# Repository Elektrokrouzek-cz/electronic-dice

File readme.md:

# Electronic dice
This is the construction of electronic dice for RedNetCon technological conference
workshop. It is based on NE555 timer and 4017 logical circuit. All components are 
in THT packages.

PCB is 2-layer and was designed using KiCad 8. Fabrication output for JLCPCB is in gerber folder.

Happy soldering!

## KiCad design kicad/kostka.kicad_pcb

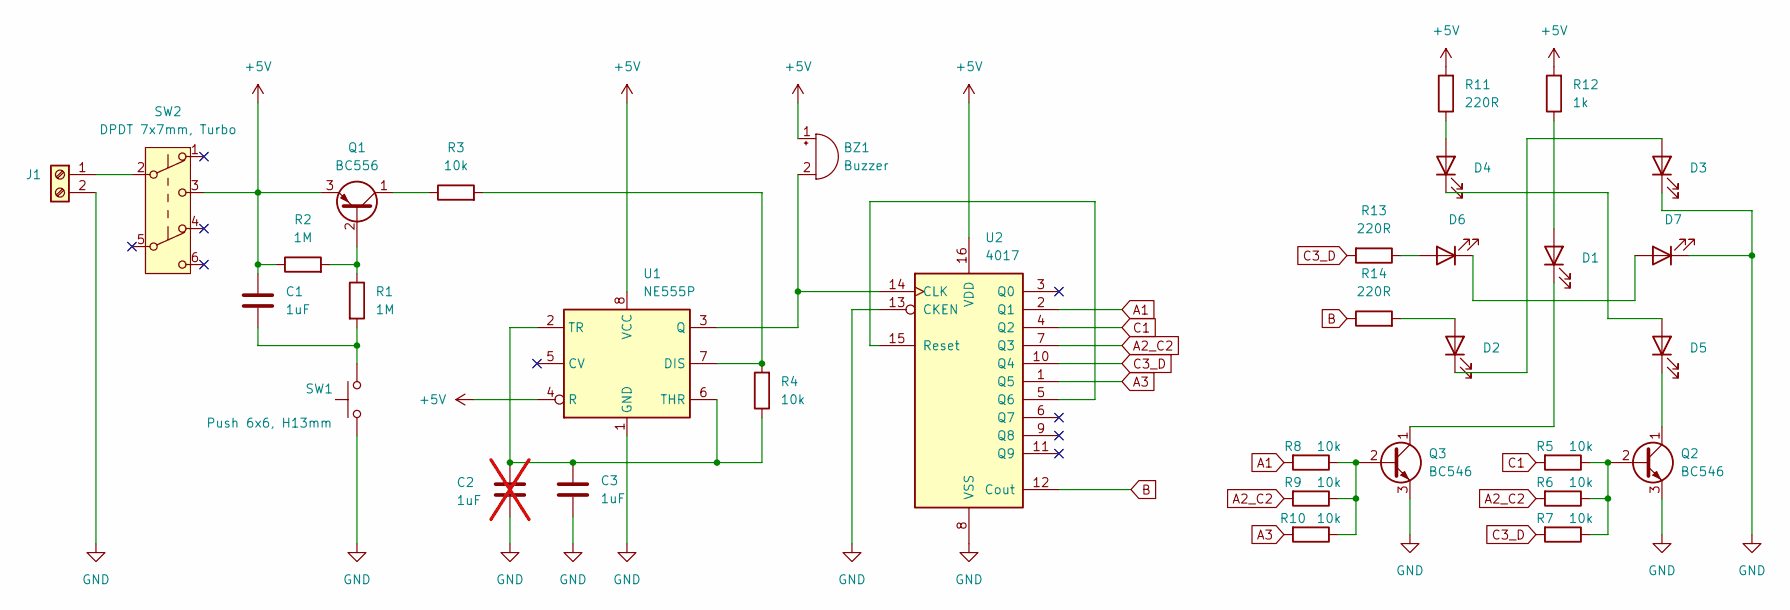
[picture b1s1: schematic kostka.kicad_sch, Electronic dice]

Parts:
BZ1: Buzzer; Buzzer_12x9.5RM7.6
C1, C3: 1uF; C_Disc_D4.3mm_W1.9mm_P5.00mm
C2: 1uF; C_Disc_D4.3mm_W1.9mm_P5.00mm; not fitted
D1, D2, D3, D4, D5, D6, D7: 5mm, R; LED_D5.0mm
J1: Screw_Terminal_01x02; TerminalBlock_4Ucon_1x02_P3.50mm_Horizontal
Q1: BC556; TO-92_Inline
Q2, Q3: BC546; TO-92_Inline
R1, R2: 1M; R_Axial_DIN0207_L6.3mm_D2.5mm_P7.62mm_Horizontal
R3, R4, R5, R6, R7, R8, R9, R10: 10k; R_Axial_DIN0207_L6.3mm_D2.5mm_P7.62mm_Horizontal
R11, R13, R14: 220R; R_Axial_DIN0207_L6.3mm_D2.5mm_P7.62mm_Horizontal
R12: 1k; R_Axial_DIN0207_L6.3mm_D2.5mm_P7.62mm_Horizontal
SW1: Push 6x6, H13mm; SW_PUSH_6mm_H13mm
SW2: DPDT 7x7mm, Turbo; SW_DPDT_7x7_Turbo
U1: NE555P; DIP-8_W7.62mm
U2: 4017; DIP-16_W7.62mm

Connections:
+5V: BZ1.1 (+), C1.1, Q1.3 (E), R2.1, R11.2, R12.2, SW2.3 (C), U1.4 (R), U1.8 (VCC), U2.16 (VDD)
A1: R8.2, U2.2 (Q1)
A2_C2: R6.2, R9.2, U2.7 (Q3)
A3: R10.2, U2.1 (Q5)
B: R14.1, U2.12 (Cout)
C1: R5.2, U2.4 (Q2)
C3_D: R7.2, R13.2, U2.10 (Q4)
GND: C2.2, C3.2, D3.1 (K), D7.1 (K), J1.2, Q2.3 (E), Q3.3 (E), SW1.1, U1.1 (GND), U2.8 (VSS), U2.13 (CKEN)
unnamed: BZ1.2 (-), U1.3 (Q), U2.14 (CLK)
unnamed: C1.2, R1.2, SW1.2
unnamed: D1.2 (A), R12.1
unnamed: D1.1 (K), Q3.1 (C)
unnamed: D2.2 (A), R14.2
unnamed: D2.1 (K), D3.2 (A)
unnamed: D4.2 (A), R11.1
unnamed: D4.1 (K), D5.2 (A)
unnamed: D5.1 (K), Q2.1 (C)
unnamed: D6.2 (A), R13.1
unnamed: D6.1 (K), D7.2 (A)
unnamed: J1.1, SW2.2 (B)
unnamed: Q1.2 (B), R1.1, R2.2
unnamed: Q1.1 (C), R3.1
unnamed: Q2.2 (B), R5.1, R6.1, R7.1
unnamed: Q3.2 (B), R8.1, R9.1, R10.1
unnamed: R3.2, R4.2, U1.7 (DIS)
unnamed: C2.1, C3.1, R4.1, U1.2 (TR), U1.6 (THR)
unnamed: U2.5 (Q6), U2.15 (Reset)

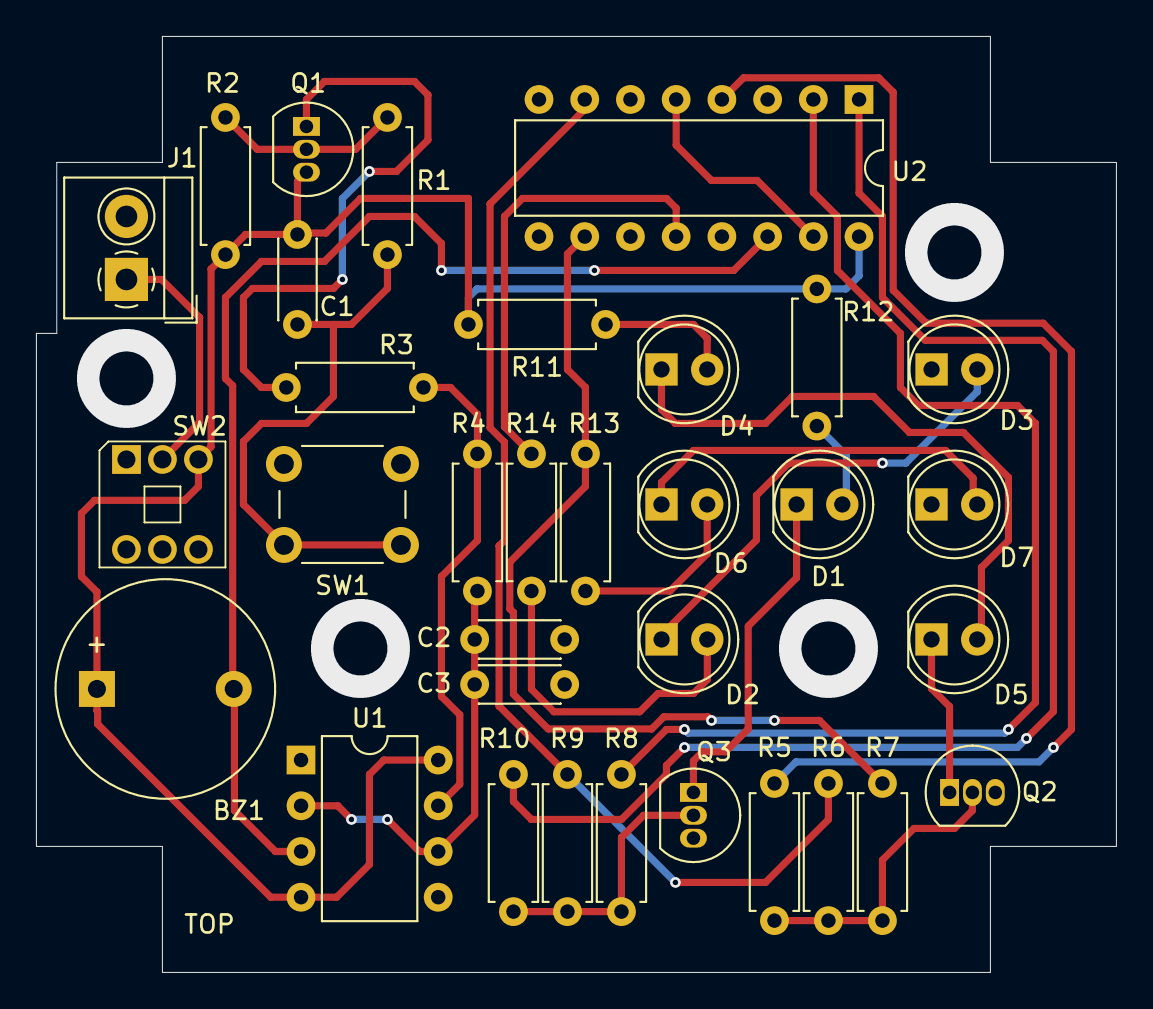
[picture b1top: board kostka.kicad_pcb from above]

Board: 2 copper layers, 60.0 x 52.0 mm, 33 parts (0 on the bottom side), 27 nets.

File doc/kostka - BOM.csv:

"Reference","Value","Datasheet","Footprint","Qty","DNP"
"BZ1","Buzzer","~","Buzzer_Beeper:Buzzer_12x9.5RM7.6","1",""
"C1,C3","1uF","~","Capacitor_THT:C_Disc_D4.3mm_W1.9mm_P5.00mm","2",""
"C2","1uF","~","Capacitor_THT:C_Disc_D4.3mm_W1.9mm_P5.00mm","1","DNP"
"D1,D2,D3,D4,D5,D6,D7","5mm, R","~","LED_THT:LED_D5.0mm","7",""
"J1","Screw_Terminal_01x02","~","TerminalBlock_4Ucon:TerminalBlock_4Ucon_1x02_P3.50mm_Horizontal","1",""
"Q1","BC556","https://www.onsemi.com/pub/Collateral/BC556BTA-D.pdf","Package_TO_SOT_THT:TO-92_Inline","1",""
"Q2,Q3","BC546","https://www.onsemi.com/pub/Collateral/BC550-D.pdf","Package_TO_SOT_THT:TO-92_Inline","2",""
"R1,R2","1M","~","Resistor_THT:R_Axial_DIN0207_L6.3mm_D2.5mm_P7.62mm_Horizontal","2",""
"R3,R4,R5,R6,R7,R8,R9,R10","10k","~","Resistor_THT:R_Axial_DIN0207_L6.3mm_D2.5mm_P7.62mm_Horizontal","8",""
"R11,R13,R14","220R","~","Resistor_THT:R_Axial_DIN0207_L6.3mm_D2.5mm_P7.62mm_Horizontal","3",""
"R12","1k","~","Resistor_THT:R_Axial_DIN0207_L6.3mm_D2.5mm_P7.62mm_Horizontal","1",""
"SW1","Push 6x6, H13mm","~","Button_Switch_THT:SW_PUSH_6mm_H13mm","1",""
"SW2","DPDT 7x7mm, Turbo","~","Button_Switch_THT_Hap:SW_DPDT_7x7_Turbo","1",""
"U1","NE555P","http://www.ti.com/lit/ds/symlink/ne555.pdf","Package_DIP:DIP-8_W7.62mm","1",""
"U2","4017","http://www.intersil.com/content/dam/Intersil/documents/cd40/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","Package_DIP:DIP-16_W7.62mm","1",""

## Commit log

2025-01-20 Housing 3D model
2025-02-10 3D models updated
2025-02-12 Manuals added
2025-02-12 Dice photo added
2025-02-12 Readme update
2025-02-18 Manual update
